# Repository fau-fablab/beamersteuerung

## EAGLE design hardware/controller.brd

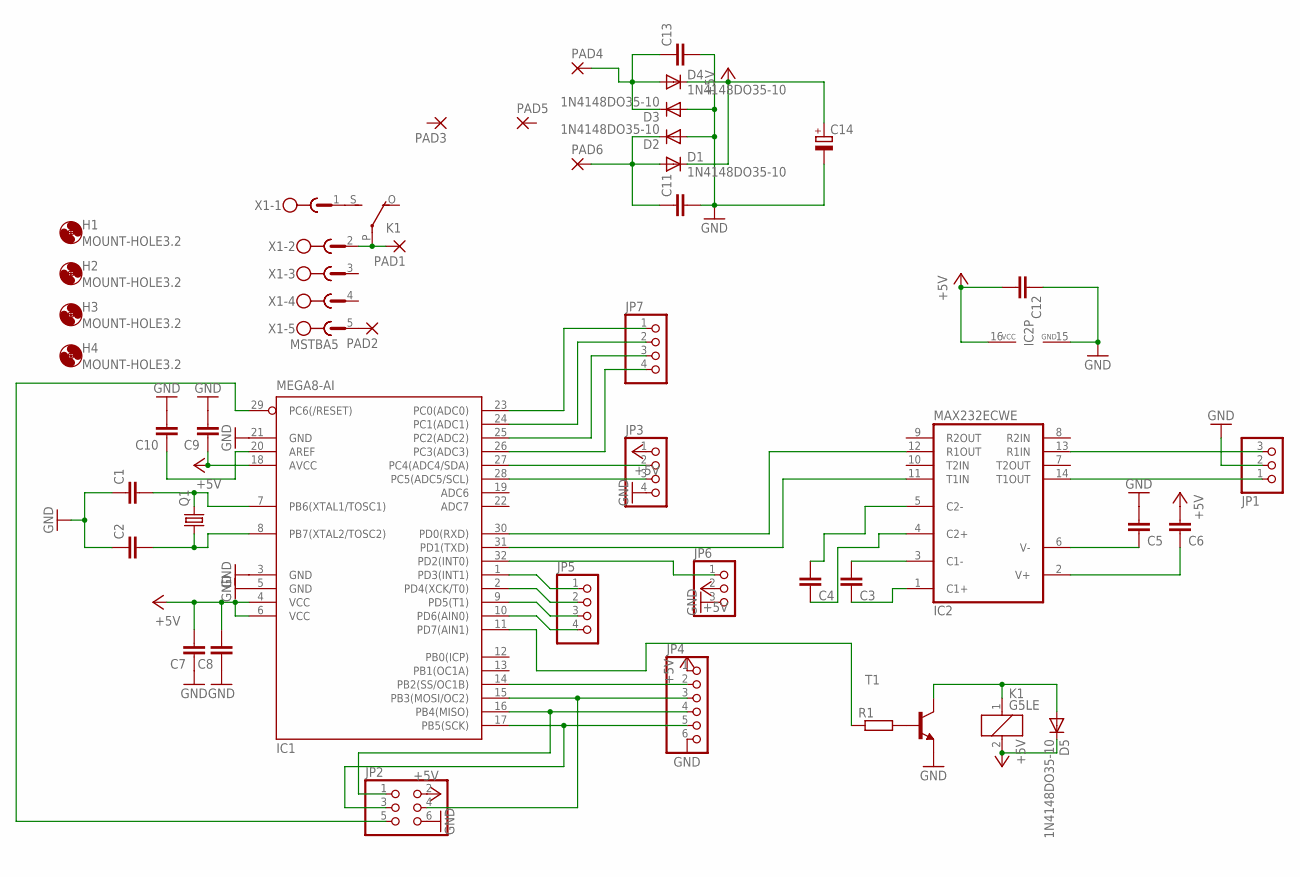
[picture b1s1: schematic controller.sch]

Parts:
C1, C2, C3, C4, C5, C6, C7, C8, C9, C10, C12: C-EUC0805; C0805
C11, C13: C-EU050-025X075; C050-025X075
C14: CPOL-EUE7.5-18; E7,5-18
D1, D2, D3, D4, D5: 1N4148DO35-10; DO35-10
H1, H2, H3, H4: MOUNT-HOLE3.2; 3,2
IC1: MEGA8-AI; TQFP32-08
IC2: MAX232ECWE; SO16
JP1, JP6: PINHD-1X3; 1X03
JP2: PINHD-2X3; 2X03
JP3, JP5, JP7: PINHD-1X4; 1X04
JP4: PINHD-1X6; 1X06
K1: G5LE
PAD1, PAD2, PAD3, PAD4, PAD5, PAD6: 3,81/1,4
Q1: CRYSTALHC49S; HC49/S
R1: R-EU_0207/10; 0207/10
T1: BC547A-NPN-TO92-CBE; TO92-CBE
X1: MSTBA5

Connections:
+5V: C6.2, C7.2, C8.2, C9.1, C12.2, C14.+, D1.C, D4.C, D5.C, IC1.4 (VCC), IC1.6 (VCC), IC1.18 (AVCC), IC2.16 (VCC), JP2.2, JP3.1, JP4.1, JP6.2, K1.2
GND: C1.1, C2.1, C5.2, C7.1, C8.1, C9.2, C10.2, C11.2, C12.1, C13.2, C14.-, D2.A, D3.A, IC1.3 (GND), IC1.5 (GND), IC1.21 (GND), IC2.15 (GND), JP1.2, JP2.6, JP3.4, JP4.6, JP6.3, T1.E
unnamed: C2.2, IC1.8 (PB7(XTAL2/TOSC2)), Q1.1
unnamed: C1.2, IC1.7 (PB6(XTAL1/TOSC1)), Q1.2
unnamed: IC1.30 (PD0(RXD)), IC2.12 (R1OUT)
unnamed: IC1.31 (PD1(TXD)), IC2.11 (T1IN)
unnamed: C3.2, IC2.3 (C1-)
unnamed: C3.1, IC2.1 (C1+)
unnamed: C4.1, IC2.4 (C2+)
unnamed: C4.2, IC2.5 (C2-)
unnamed: C5.1, IC2.6 (V-)
unnamed: C6.1, IC2.2 (V+)
unnamed: K1.P, PAD1.1, X1.2
unnamed: IC2.14 (T1OUT), JP1.1
unnamed: IC2.13 (R1IN), JP1.3
unnamed: IC1.16 (PB4(MISO)), JP2.1, JP4.4
unnamed: IC1.17 (PB5(SCK)), JP2.3, JP4.5
unnamed: IC1.29 (PC6(/RESET)), JP2.5
unnamed: IC1.15 (PB3(MOSI/OC2)), JP2.4, JP4.3
unnamed: C10.1, IC1.20 (AREF)
unnamed: IC1.23 (PC0(ADC0)), JP7.1
unnamed: IC1.24 (PC1(ADC1)), JP7.2
unnamed: IC1.25 (PC2(ADC2)), JP7.3
unnamed: IC1.26 (PC3(ADC3)), JP7.4
unnamed: IC1.27 (PC4(ADC4/SDA)), JP3.2
unnamed: IC1.28 (PC5(ADC5/SCL)), JP3.3
unnamed: IC1.14 (PB2(SS/OC1B)), JP4.2
unnamed: IC1.32 (PD2(INT0)), JP6.1
unnamed: R1.2, T1.B
unnamed: IC1.2 (PD4(XCK/T0)), JP5.2
unnamed: IC1.9 (PD5(T1)), JP5.3
unnamed: IC1.10 (PD6(AIN0)), JP5.4
unnamed: IC1.11 (PD7(AIN1)), R1.1
unnamed: K1.S, X1.1
unnamed: PAD2.1, X1.5
unnamed: C11.1, D1.A, D2.C, PAD6.1
unnamed: IC1.1 (PD3(INT1)), JP5.1
unnamed: C13.1, D3.C, D4.A, PAD4.1
unnamed: D5.A, K1.1, T1.C

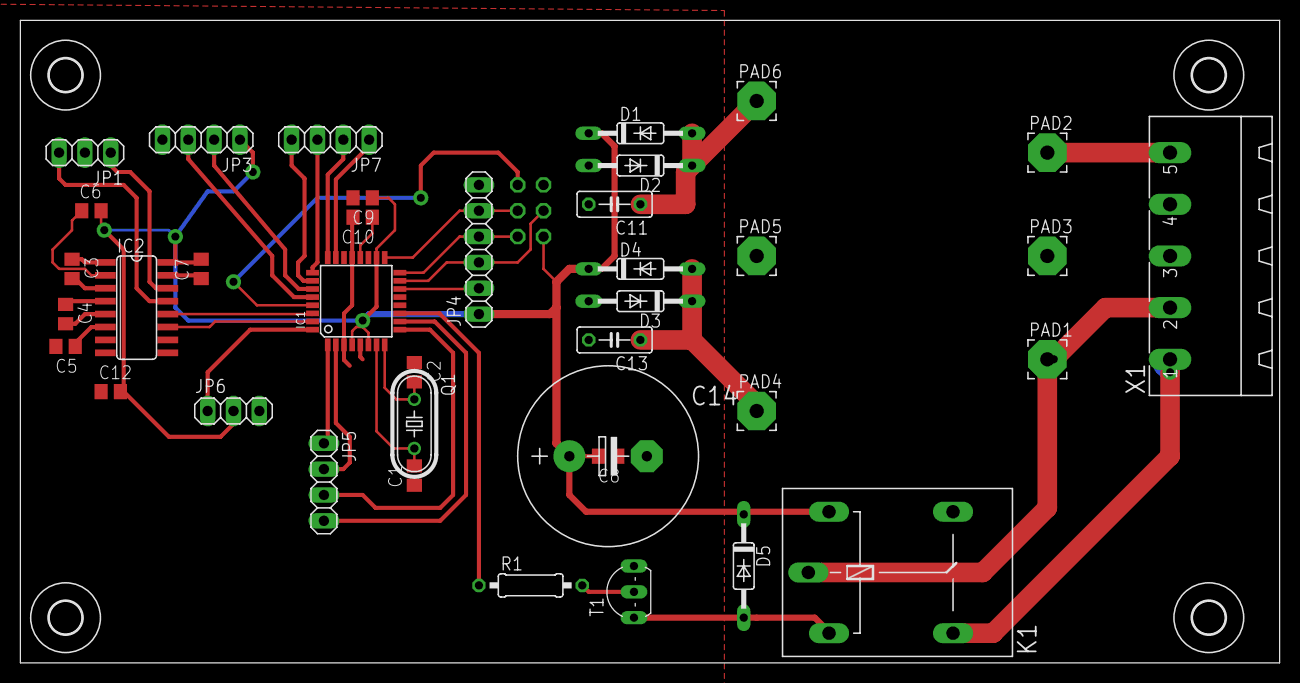
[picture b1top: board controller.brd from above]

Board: 2 copper layers, 123.8 x 63.2 mm, 43 parts (1 on the bottom side), 39 nets.

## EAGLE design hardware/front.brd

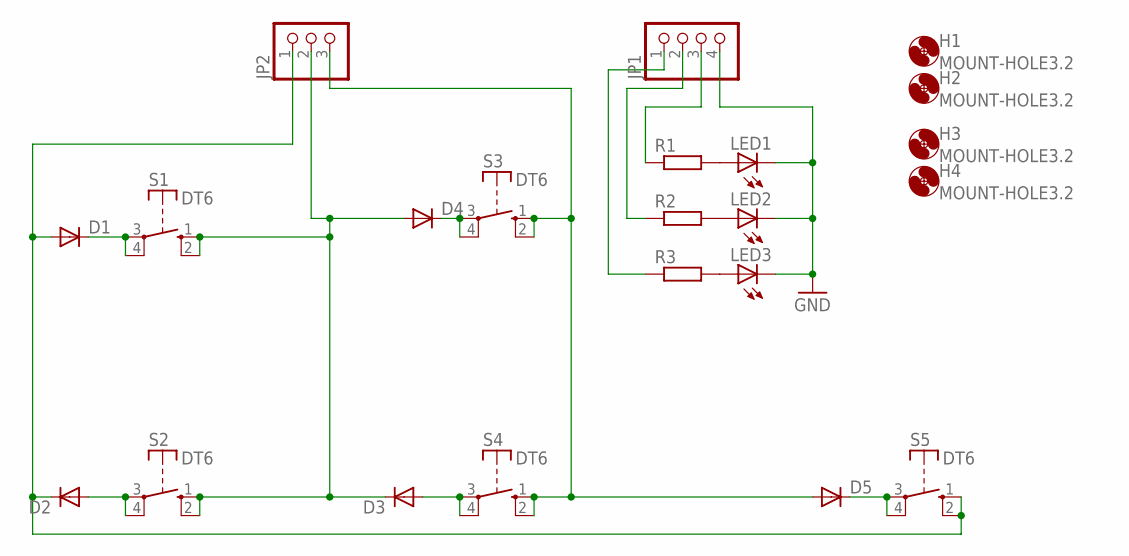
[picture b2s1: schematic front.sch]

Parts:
D1, D2, D3, D4, D5: DIODE-MINIMELF; MINIMELF
H1, H2, H3, H4: MOUNT-HOLE3.2; 3,2
JP1: PINHD-1X4; 1X04
JP2: PINHD-1X3; 1X03
LED1, LED2, LED3: LED3MM
R1, R2, R3: R-EU_R0805; R0805
S1, S2, S3, S4, S5: DT6

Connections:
GND: JP1.4, LED1.K (C), LED2.K (C), LED3.K (C)
unnamed: LED1.A, R1.2
unnamed: LED2.A, R2.2
unnamed: LED3.A, R3.2
unnamed: JP1.3, R1.1
unnamed: JP1.2, R2.1
unnamed: JP1.1, R3.1
unnamed: D1.C, S1.3, S1.4
unnamed: D2.A, S2.3, S2.4
unnamed: D4.C, S3.3, S3.4
unnamed: D3.A, S4.3, S4.4
unnamed: D3.C, D4.A, JP2.2, S1.1 (S), S1.2 (S), S2.1 (S), S2.2 (S)
unnamed: D5.A, JP2.3, S3.1 (S), S3.2 (S), S4.1 (S), S4.2 (S)
unnamed: D1.A, D2.C, JP2.1, S5.1 (S), S5.2 (S)
unnamed: D5.C, S5.3, S5.4

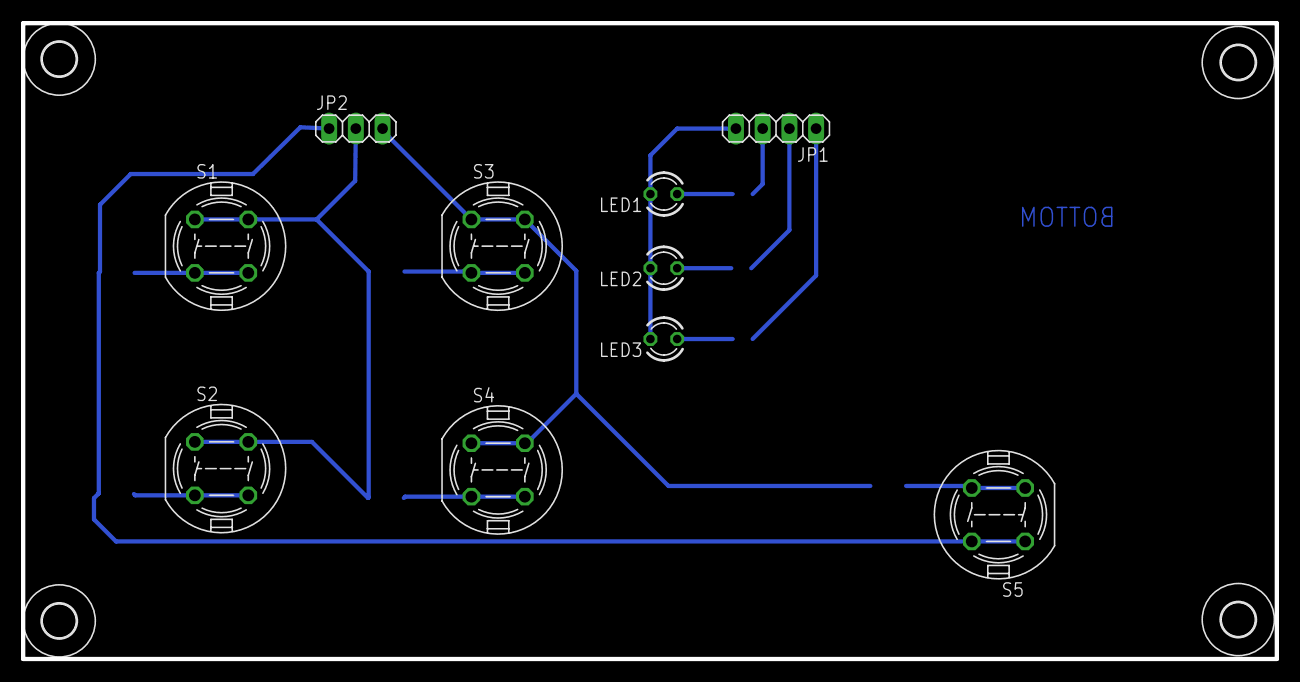
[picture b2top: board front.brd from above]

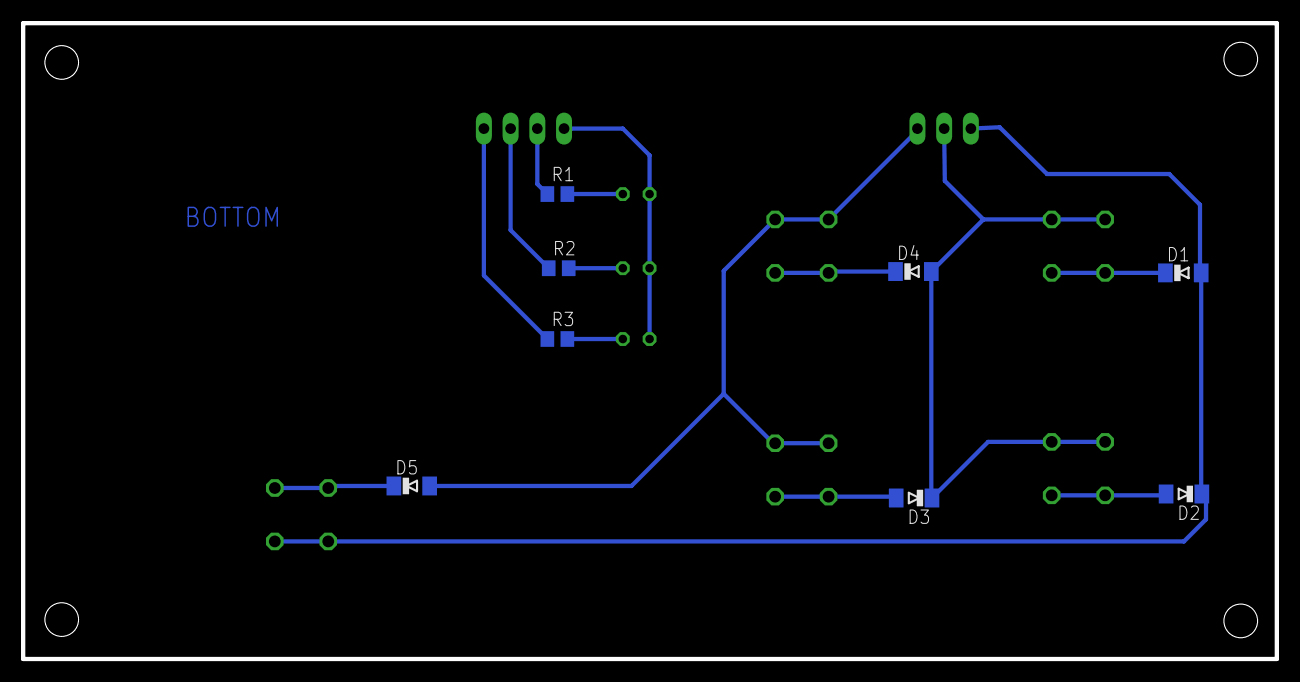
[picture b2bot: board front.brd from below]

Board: 2 copper layers, 119.2 x 60.4 mm, 22 parts (8 on the bottom side), 15 nets.

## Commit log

2015-01-22 hardware verschoben
2015-01-23 firmware added
2015-01-23 pragma once -> include guards
2015-01-23 pdf fuer die kicadler
2015-01-29 minor pcb changes
2015-05-12 Screen control works now
